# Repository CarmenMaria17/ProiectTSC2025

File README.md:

# TSC2025 Project

## Block Diagram

## Brief Description

### Microcontroller
- **ESP32-C6**: Main processor with WiFi/BLE, controls all components

### Display and Storage
- **E-Ink Display**: Minimal power consumption display
- **SD Card**: Electronic book storage
- **64MB Flash Memory**: For firmware and cache

### Power
- **USB-C**: Charging and data transfer
- **Battery charging circuit**: MCP73831 for LiPo battery
- **LiPo Battery**: 3.7V portable power
- **3.3V Regulator**: Voltage stabilizer for ESP32 and sensors

### Sensors
- **BME680**: Temperature and humidity, I2C connection

### Other Components
- **RTC DS3231**: Real-time clock for timekeeping
- **Buttons**: Navigation and control via GPIO

### Interfaces
- **SPI**: Display, SD card, flash memory
- **I2C**: Sensors, RTC
- **GPIO**: Buttons and control

## ESP32-C6 - Pin Allocation

### Communication pins
- **SPI_CLK**: Clock for SPI interface (connected to Flash, SD Card, Display)
- **SPI_MOSI**: Master Out Slave In for SPI
- **SPI_MISO**: Master In Slave Out for SPI
- **SS_SD**: Chip Select for SD Card
- **SS_FLASH**: Chip Select for Flash memory
- **SS_DISP**: Chip Select for E-Ink Display
- **I2C_SCL**: Clock for I2C interface
- **I2C_SDA**: Data line for I2C
- **EPD_DC**: Data/Command for E-Ink display
- **EPD_RST**: Reset for E-Ink display
- **EPD_BUSY**: Status signal from E-Ink display

### Other specific pins
- **RTC_INT**: Interrupt from RTC module
- **VBAT**: Battery power
- **3V3**: 3.3V power
- **GND**: Ground

# Bill of Materials

| Component | Model | Datasheet |
|-----------|--------------|-----------|
| BD5229G-TR | [Model](https://www.digikey.ee/en/models/658502) | [Datasheet](https://www.rohm.com/datasheet?p=BD5229G&dist=Digi-key&media=referral&source=digi-key.com&campaign=Digi-key) |
| ESP32 WROVER 0805 Capacitor | [Model](https://ro.mouser.com/ProductDetail/KYOCERA-AVX/SD0805S020S1R0?qs=jCA%252BPfw4LHbpkAoSnwrdjw%3D%3D) | [Datasheet](https://ro.mouser.com/datasheet/2/40/schottky-3165252.pdf) |
| 112A-TAAR-R03 | [Model](https://www.snapeda.com/parts/112A-TAAR-R03/Attend/view-part/) | [Datasheet](https://www.snapeda.com/parts/112A-TAAR-R03/Attend/datasheet/) |
| 744043680 | [Model](https://ro.mouser.com/ProductDetail/Wurth-Elektronik/744043680?qs=PGXP4M47uW6VkZq%252BkzjrHA%3D%3D) | [Datasheet](https://www.we-online.com/components/products/datasheet/744043680.pdf) |
| LED Chip 0603 | [Model](https://grabcad.com/library/0603-smd-led-1) | [Datasheet](https://www.snapeda.com/parts/KP-1608SURCK/Kingbright/datasheet/) |
| MAX17048G+T10 | [Model](https://www.snapeda.com/parts/MAX17048G+T10/Analog+Devices/view-part/?ref=eda) | [Datasheet](https://www.snapeda.com/parts/MAX17048G+T10/Analog%20Devices/datasheet/) |
| MBR0530 Schottky Diode | [Model](https://www.snapeda.com/parts/MBR0530/Onsemi/view-part/?ref=eda) | [Datasheet](https://www.snapeda.com/parts/MBR0530/ON%20Semiconductor/datasheet/) |
| PGB1010603MR | [Model](https://www.snapeda.com/parts/PGB1010603MR/Littelfuse/view-part/?ref=eda) | [Datasheet](https://www.snapeda.com/parts/PGB1010603MR/Littelfuse%20Inc./datasheet/) |
| QWIIC Connector | [Model](https://www.snapeda.com/parts/PRT-14417/SparkFun/view-part/) | [Datasheet](https://www.snapeda.com/parts/PRT-14417/SparkFun%20Electronics/datasheet/) |
| ESP32 WROVER BME680 Sensor | [Model](https://www.digikey.ro/en/models/7401317) | [Datasheet](https://www.bosch-sensortec.com/media/boschsensortec/downloads/datasheets/bst-bme680-ds001.pdf) |
| FH34SRJ-24S-0.5SH | [Model](https://www.snapeda.com/parts/FH34SRJ-24S-0.5SH(99)/Hirose/view-part/) | [Datasheet](https://www.snapeda.com/parts/FH34SRJ-24S-0.5SH(99)/Hirose%20Connector/datasheet/) |
| Resistor 0402 | [Model](https://componentsearchengine.com/part-view/R0402%201%25%20100%20K%20(RC0402FR-07100KL)/YAGEO) | [Datasheet](https://www.yageo.com/upload/media/product/products/datasheet/rchip/PYu-RC_Group_51_RoHS_L_12.pdf) |
| ESP32 WROVER MCP73831 Power Management | [Model](https://www.snapeda.com/parts/MCP73831T-2ACI/OT/Microchip/view-part/) | [Datasheet](https://www.snapeda.com/parts/MCP73831T-2ACI/OT/Microchip/datasheet/) |
| ESP32C6 Varistor 1812 | [Model](https://www.snapeda.com/parts/RC0603JR-070RL/Yageo/view-part/) | [Datasheet](https://www.snapeda.com/parts/RC0603JR-070RL/Yageo/datasheet/) |
| ESP32C6 WROOM-1-N8 | [Model](https://www.snapeda.com/parts/ESP32-C6-WROOM-1-N8/Espressif+Systems/view-part/?ref=eda) | [Datasheet](https://www.snapeda.com/parts/ESP32-C6-WROOM-1-N8/Espressif%20Systems/datasheet/) |
| Capacitor 0402 | [Model](https://componentsearchengine.com/part-view/CC0402MRX5R5BB106/YAGEO) | [Datasheet](https://componentsearchengine.com/Datasheets/2/CC0402MRX5R5BB106.pdf) |
| SI1308EDL-T1-GE3 MOSFET | [Model](https://www.snapeda.com/parts/SI1308EDL-T1-GE3/Vishay+Siliconix/view-part/?ref=eda) | [Datasheet](https://www.snapeda.com/parts/SI1308EDL-T1-GE3/Vishay%20Siliconix/datasheet/) |
| SJ | [Model](https://grabcad.com/library/solder-jumpers-1) | [Datasheet]() |
| CPH3225A | [Model](https://www.snapeda.com/parts/CPH3225A/Seiko+Instruments/view-part/?ref=eda) | [Datasheet](https://www.snapeda.com/parts/CPH3225A/Seiko%20Instruments/datasheet/) |
| Button | [Model](https://industry.panasonic.com/global/en/products/control/switch/light-touch/number/evqpuj02k) | [Datasheet](https://industry.panasonic.com/global/en/downloads?tab=catalog&small_g_cd=203&part_no=EVQPUJ02K) |
| DS3231SN | [Model](https://www.snapeda.com/parts/DS3231SN%23/Analog+Devices/view-part/?ref=eda) | [Datasheet](https://www.snapeda.com/parts/DS3231SN%23/Analog%20Devices/datasheet/) |
| USBLC6-2SC6Y | [Model](https://www.snapeda.com/parts/USBLC6-2SC6Y/STMicroelectronics/view-part/?ref=eda) | [Datasheet](https://www.snapeda.com/parts/USBLC6-2SC6Y/STMicroelectronics/datasheet/) |
| W25Q512JVEIQ | [Model](https://www.digikey.ro/en/models/10244706) | [Datasheet](https://www.winbond.com/resource-files/W25Q512JV%20SPI%20RevB%2006252019%20KMS.pdf) |
| XC6220A331MR-G | [Model](https://componentsearchengine.com/part-view/XC6220A331MR-G/Torex) | [Datasheet](https://product.torexsemi.com/system/files/series/xc6220.pdf) |
| TPTP20R | [Model](https://ro.mouser.com/ProductDetail/Adafruit/3825?qs=%252bEew9%252b0nqrAn6n76%252bB5vZg%3D%3D&utm_source=findchips&utm_medium=aggregator&utm_campaign=3825&utm_term=3825&utm_content=Adafruit&_gl=1*1t6jdbp*_ga*MTQ5NTQ1ODI1LjE3NDMyMzgzNTY.*_ga_15W4STQT4T*MTc0Mzc4MDU5Ni4xMi4xLjE3NDM3ODM2MzIuNDIuMC4w) | [Datasheet](https://cdn-shop.adafruit.com/product-files/3825/3825_diagram.PDF) |
| USB4110-GF-A | [Model](https://componentsearchengine.com/part-view/USB4110-GF-A/GCT%20(GLOBAL%20CONNECTOR%20TECHNOLOGY)) | [Datasheet](https://gct.co/files/drawings/usb4110.pdf) |

# Power Consumption Estimation

The ESP32-C6 microcontroller with Wi-Fi active draws approximately 200mA at 3.3V, consuming around 660mW of power.

For display operations, the 1.5" E-Ink display requires about 40mA (132mW) during refresh cycles.

The BME680 environmental sensor consumes minimal power at just 3.1mA (10.23mW) during measurement operations and can be put into sleep mode between readings.

The DS3231 RTC module is extremely efficient, drawing only 0.15mA (0.495mW) while maintaining accurate timekeeping.

Storage components include the SD card for e-book storage that requires 50mA (165mW) during active read/write operations, and the 64MB external flash memory that draws about 25mA (82.5mW) when accessed.

In total, the maximum estimated power consumption is approximately 318.25mA at 3.3V, resulting in 1050.72mW during peak usage.

# Other images

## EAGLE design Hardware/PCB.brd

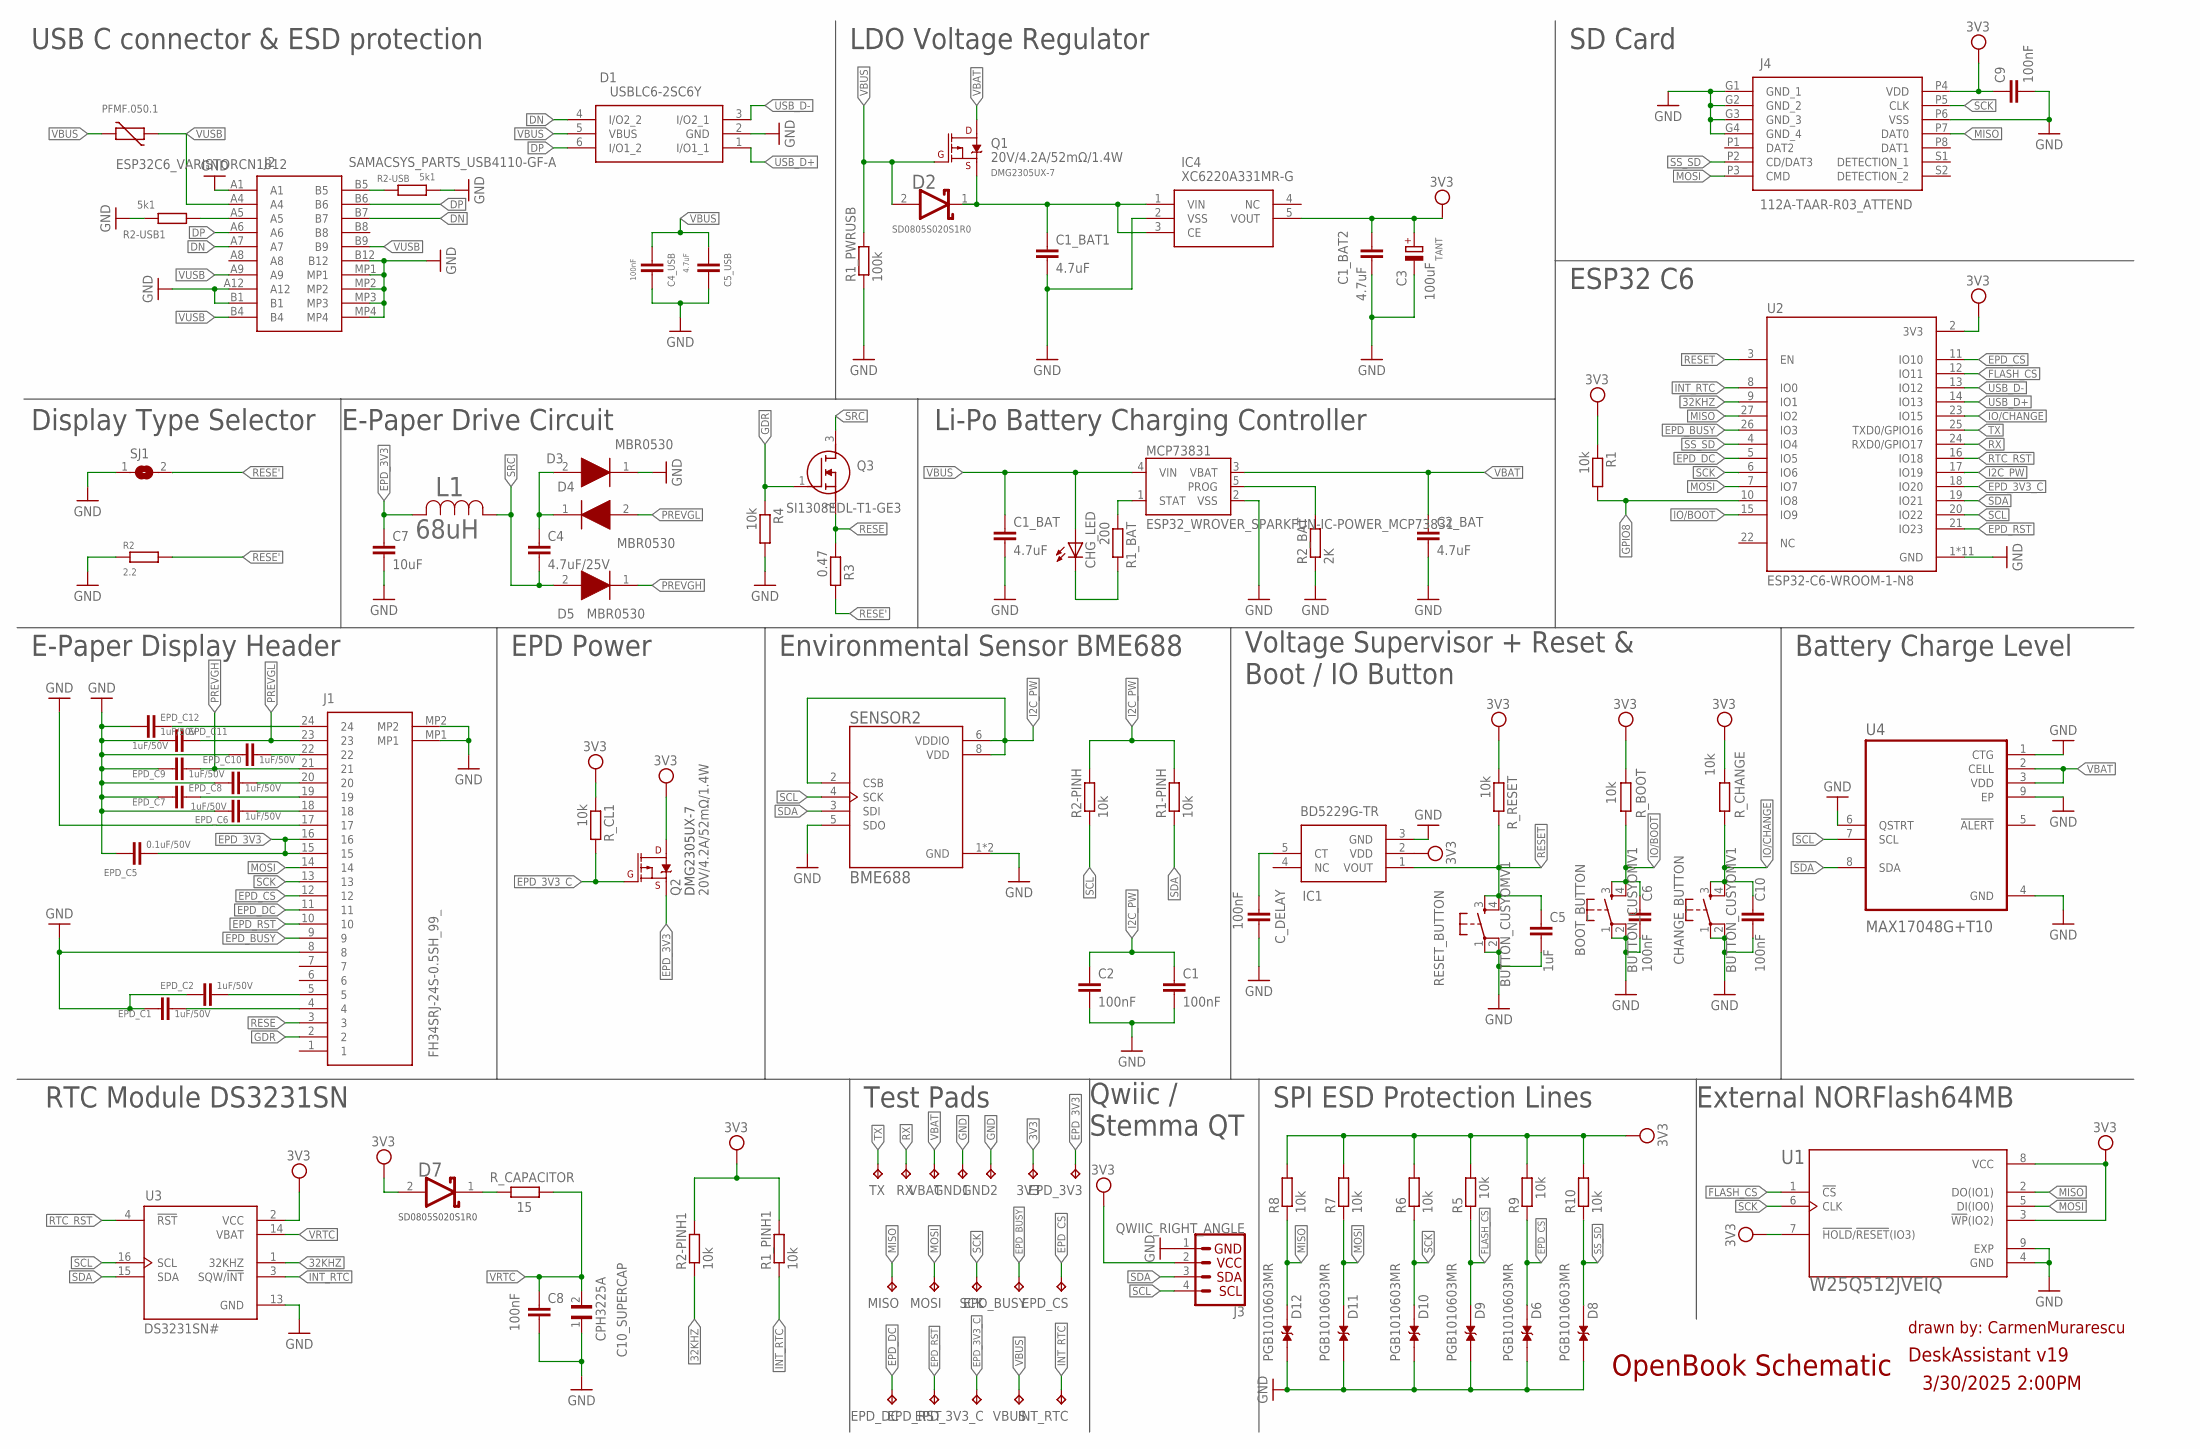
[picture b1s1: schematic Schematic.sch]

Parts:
3V3: TPTP20R; TP20R
BOOT_BUTTON: BUTTON_CUSYOMV1; MYBUTTON
C1, C2, C4_USB, C6, C8, C9, C10: 100nF; ESP32_WROVER_EAGLE-LTSPICE_C0402
C1_BAT, C1_BAT1, C1_BAT2, C2_BAT, C5_USB: 4.7uF; ESP32_WROVER_EAGLE-LTSPICE_C0402
C3: 100uF; RCL_CT3528
C4: 4.7uF/25V; ESP32_WROVER_EAGLE-LTSPICE_C0402
C5: 1uF; ESP32_WROVER_EAGLE-LTSPICE_C0402
C7: 10uF; ESP32_WROVER_EAGLE-LTSPICE_C0402
C10_SUPERCAP: CPH3225A; CAPCP3225X100N
CHANGE_BUTTON: BUTTON_CUSYOMV1; MYBUTTON
CHG_LED: ADAFRUIT_LEDCHIP-LED0603; ADAFRUIT_CHIP-LED0603
C_DELAY: 100nF; ESP32_WROVER_EAGLE-LTSPICE_C0402
D1: USBLC6-2SC6Y; SOT95P280X145-6N
D2: ESP32_WROVER_AVX---SD0805S020S1R0_AVX_SD0805S020S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; ESP32_WROVER_AVX---SD0805S020S1R0_AVX_SD0805S020S1R0_0
D3, D4, D5: MBR0530; SOD3716X135N
D6, D8, D9, D10, D11, D12: PGB1010603MR; DIOC1608X36N
D7: SD0805S020S1R0; ESP32_WROVER_AVX---SD0805S020S1R0_AVX_SD0805S020S1R0_0
EPD_3V3, EPD_3V3_C: TPTP20R; TP20R
EPD_BUSY: TPTP20R; TP20R
EPD_C1, EPD_C2, EPD_C6, EPD_C7, EPD_C8, EPD_C9, EPD_C10, EPD_C11, EPD_C12: 1uF/50V; ESP32_WROVER_EAGLE-LTSPICE_C0402
EPD_C5: 0.1uF/50V; ESP32_WROVER_EAGLE-LTSPICE_C0402
EPD_CS: TPTP20R; TP20R
EPD_DC: TPTP20R; TP20R
EPD_RST: TPTP20R; TP20R
GND1, GND2: TPTP20R; TP20R
IC1: BD5229G-TR; SOT95P280X120-5N
IC4: XC6220A331MR-G; SOT95P280X120-5N
INT_RTC: TPTP20R; TP20R
J1: FH34SRJ-24S-0.5SH_99_; FH34SRJ24S05SH99
J2: SAMACSYS_PARTS_USB4110-GF-A; SAMACSYS_PARTS_USB4110GFA
J3: QWIIC_RIGHT_ANGLE; JST04_1MM_RA
J4: 112A-TAAR-R03_ATTEND; 112ATAARR03ATTEND
L1: 68uH; IND_4828-WE-TPC_WRE
MCP73831: ESP32_WROVER_SPARKFUN-IC-POWER_MCP73831; ESP32_WROVER_SPARKFUN-IC-POWER_SOT23-5
MISO: TPTP20R; TP20R
MOSI: TPTP20R; TP20R
PFMF.050.1: ESP32C6_VARISTORCN1812; ESP32C6_VARISTOR_CT/CN1812
Q1, Q2: 20V/4.2A/52mΩ/1.4W; ESP32_WROVER_SPARKFUN-DISCRETESEMI_SOT23-3
Q3: SI1308EDL-T1-GE3; SOT65P210X110-3N
R1, R1-PINH, R1_PINH1, R2-PINH, R2-PINH1, R4, R5, R6, R7, R8, R9, R10: 10k; ESP32_WROVER_EAGLE-LTSPICE_R0402
R1_BAT: 200; ESP32_WROVER_EAGLE-LTSPICE_R0402
R1_PWRUSB: 100k; ESP32_WROVER_EAGLE-LTSPICE_R0402
R2: 2.2; ESP32_WROVER_EAGLE-LTSPICE_R0402
R2-USB, R2-USB1: 5k1; ESP32_WROVER_EAGLE-LTSPICE_R0402
R2_BAT: 2K; ESP32_WROVER_EAGLE-LTSPICE_R0402
R3: 0.47; ESP32_WROVER_EAGLE-LTSPICE_R0402
RESET_BUTTON: BUTTON_CUSYOMV1; MYBUTTON
RX: TPTP20R; TP20R
R_BOOT: 10k; ESP32_WROVER_EAGLE-LTSPICE_R0402
R_CAPACITOR: 15; ESP32_WROVER_EAGLE-LTSPICE_R0402
R_CHANGE: 10k; ESP32_WROVER_EAGLE-LTSPICE_R0402
R_CL1: 10k; ESP32_WROVER_EAGLE-LTSPICE_R0402
R_RESET: 10k; ESP32_WROVER_EAGLE-LTSPICE_R0402
SCK: TPTP20R; TP20R
SENSOR2: BME688; ESP32_WROVER_BME680_PSON80P300X300X100-8N
SJ1: SJ
TX: TPTP20R; TP20R
U1: W25Q512JVEIQ; SON127P600X800X80-9N
U2: ESP32-C6-WROOM-1-N8; XCVR_ESP32-C6-WROOM-1-N8
U3: DS3231SN#; SOIC127P1032X265-16N
U4: MAX17048G+T10; SON50P200X200X80-9N
VBAT: TPTP20R; TP20R
VBUS: TPTP20R; TP20R

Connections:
3V3: 3V3.TP, C1_BAT2.1, C3.+, C9.1, D7.2 (ANODE), IC1.2 (VDD), IC4.5 (VOUT), J3.2, J4.P4 (VDD), Q2.3 (D), R1.1, R1_PINH1.2, R2-PINH1.2, R5.2, R6.2, R7.2, R8.2, R9.2, R10.2, R_BOOT.2, R_CHANGE.2, R_CL1.1, R_RESET.1, U1.3 (!WP!(IO2)), U1.7 (!HOLD!/!RESET!(IO3)), U1.8 (VCC), U2.2 (3V3), U3.2 (VCC)
32KHZ: R2-PINH1.1, U2.9 (IO1), U3.1 (32KHZ)
DN: D1.4 (I/O2_2), J2.A7, J2.B7
DP: D1.6 (I/O1_2), J2.A6, J2.B6
EPD_3V3: C7.1, EPD_3V3.TP, EPD_C5.1, J1.15, J1.16, L1.2, Q2.2 (S)
EPD_3V3_C: EPD_3V3_C.TP, Q2.1 (G), R_CL1.2, U2.18 (IO20)
EPD_BUSY: EPD_BUSY.TP, J1.9, U2.26 (IO3)
EPD_CS: D6.2, EPD_CS.TP, J1.12, R9.1, U2.11 (IO10)
EPD_DC: EPD_DC.TP, J1.11, U2.5 (IO5)
EPD_RST: EPD_RST.TP, J1.10, U2.21 (IO23)
FLASH_CS: D9.2, R5.1, U1.1 (!CS), U2.12 (IO11)
GDR: J1.2, Q3.1 (G), R4.1
GND: BOOT_BUTTON.1, BOOT_BUTTON.2, C1.2, C1_BAT.2, C1_BAT1.2, C1_BAT2.2, C2.2, C2_BAT.2, C3.-, C4_USB.2, C5.2, C5_USB.2, C6.2, C7.2, C8.2, C9.2, C10.2, C10_SUPERCAP.1, CHANGE_BUTTON.1, CHANGE_BUTTON.2, C_DELAY.2, D1.2 (GND), D4.1 (K), D6.1, D8.1, D9.1, D10.1, D11.1, D12.1, EPD_C1.2, EPD_C2.2, EPD_C5.2, EPD_C6.2, EPD_C7.2, EPD_C8.2, EPD_C9.2, EPD_C10.2, EPD_C11.2, EPD_C12.2, GND1.TP, GND2.TP, IC1.3 (GND), IC4.2 (VSS), J1.8, J1.17, J1.MP1, J1.MP2, J2.A1, J2.A12, J2.B1, J2.B12, J2.MP1, J2.MP2, J2.MP3, J2.MP4, J3.1, J4.G1 (GND_1), J4.G2 (GND_2), J4.G3 (GND_3), J4.G4 (GND_4), J4.P6 (VSS), MCP73831.2 (VSS), R1_PWRUSB.1, R2.1, R2-USB.2, R2-USB1.1, R2_BAT.1, R4.2, RESET_BUTTON.1, RESET_BUTTON.2, SENSOR2.1 (GND), SENSOR2.5 (SDO), SENSOR2.7 (GND), SJ1.1, U1.4 (GND), U1.9 (EXP), U2.1 (GND), U2.28 (GND), U2.29_1 (GND), U2.29_2 (GND), U2.29_3 (GND), U2.29_4 (GND), U2.29_5 (GND), U2.29_6 (GND), U2.29_7 (GND), U2.29_8 (GND), U2.29_9 (GND), U3.13 (GND), U4.1 (CTG), U4.4 (GND), U4.6 (QSTRT), U4.9 (EP)
GPIO8: R1.2, U2.10 (IO8)
I2C_PW: C1.1, C2.1, R1-PINH.2, R2-PINH.2, SENSOR2.2 (CSB), SENSOR2.6 (VDDIO), SENSOR2.8 (VDD), U2.17 (IO19)
INT_RTC: INT_RTC.TP, R1_PINH1.1, U2.8 (IO0), U3.3 (SQW/!INT)
IO/BOOT: BOOT_BUTTON.3, BOOT_BUTTON.4, C6.1, R_BOOT.1, U2.15 (IO9)
IO/CHANGE: C10.1, CHANGE_BUTTON.3, CHANGE_BUTTON.4, R_CHANGE.1, U2.23 (IO15)
MISO: D12.2, J4.P7 (DAT0), MISO.TP, R8.1, U1.2 (DO(IO1)), U2.27 (IO2)
MOSI: D11.2, J1.14, J4.P3 (CMD), MOSI.TP, R7.1, U1.5 (DI(IO0)), U2.7 (IO7)
unnamed: J2.A5, R2-USB1.2
unnamed: J2.B5, R2-USB.1
unnamed: C1_BAT1.1, D2.1 (CATHODE), IC4.1 (VIN), IC4.3 (CE), Q1.2 (S)
unnamed: C4.1, D3.1 (K), D4.2 (A)
unnamed: CHG_LED.C, R1_BAT.2
unnamed: MCP73831.1 (STAT), R1_BAT.1
unnamed: EPD_C6.1, J1.18
unnamed: MCP73831.5 (PROG), R2_BAT.2
unnamed: EPD_C1.1, J1.4
unnamed: EPD_C2.1, J1.5
unnamed: EPD_C7.1, J1.19
unnamed: EPD_C8.1, J1.20
unnamed: D7.1 (CATHODE), R_CAPACITOR.2
unnamed: EPD_C10.1, J1.22
unnamed: C_DELAY.1, IC1.5 (CT)
unnamed: EPD_C12.1, J1.24
PREVGH: D5.1 (K), EPD_C9.1, J1.21
PREVGL: D3.2 (A), EPD_C11.1, J1.23
RESE: J1.3, Q3.2 (S), R3.1
RESE': R2.2, R3.2, SJ1.2
RESET: C5.1, IC1.1 (VOUT), RESET_BUTTON.3, RESET_BUTTON.4, R_RESET.2, U2.3 (EN)
RTC_RST: U2.16 (IO18), U3.4 (!RST)
RX: RX.TP, U2.24 (RXD0/GPIO17)
SCK: D10.2, J1.13, J4.P5 (CLK), R6.1, SCK.TP, U1.6 (CLK), U2.6 (IO6)
SCL: J3.4, R2-PINH.1, SENSOR2.4 (SCK), U2.20 (IO22), U3.16 (SCL), U4.7 (SCL)
SDA: J3.3, R1-PINH.1, SENSOR2.3 (SDI), U2.19 (IO21), U3.15 (SDA), U4.8 (SDA)
SRC: C4.2, D5.2 (A), L1.1, Q3.3 (D)
SS_SD: D8.2, J4.P2 (CD/DAT3), R10.1, U2.4 (IO4)
TX: TX.TP, U2.25 (TXD0/GPIO16)
USB_D+: D1.1 (I/O1_1), U2.14 (IO13)
USB_D-: D1.3 (I/O2_1), U2.13 (IO12)
VBAT: C2_BAT.1, MCP73831.3 (VBAT), Q1.3 (D), U4.2 (CELL), U4.3 (VDD), VBAT.TP
VBUS: C1_BAT.1, C4_USB.1, C5_USB.1, CHG_LED.A, D1.5 (VBUS), D2.2 (ANODE), MCP73831.4 (VIN), PFMF.050.1.2, Q1.1 (G), R1_PWRUSB.2, VBUS.TP
VRTC: C8.1, C10_SUPERCAP.2, R_CAPACITOR.1, U3.14 (VBAT)
VUSB: J2.A4, J2.A9, J2.B4, J2.B9, PFMF.050.1.1

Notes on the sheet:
USB C connector & ESD protection
LDO Voltage Regulator
SD Card
Display Type Selector
E-Paper Drive Circuit
Li-Po Battery Charging Controller
ESP32 C6
E-Paper Display Header
EPD Power
Environmental Sensor BME688
Voltage Supervisor + Reset & Boot / IO Button
Battery Charge Level
RTC Module DS3231SN
Test Pads
Qwiic / Stemma QT
SPI ESD Protection Lines
External NORFlash64MB
OpenBook Schematic
drawn by: CarmenMurarescu
DeskAssistant v19
3/30/2025 2:00PM
DMG2305UX-7
SD0805S020S1R0
TANT

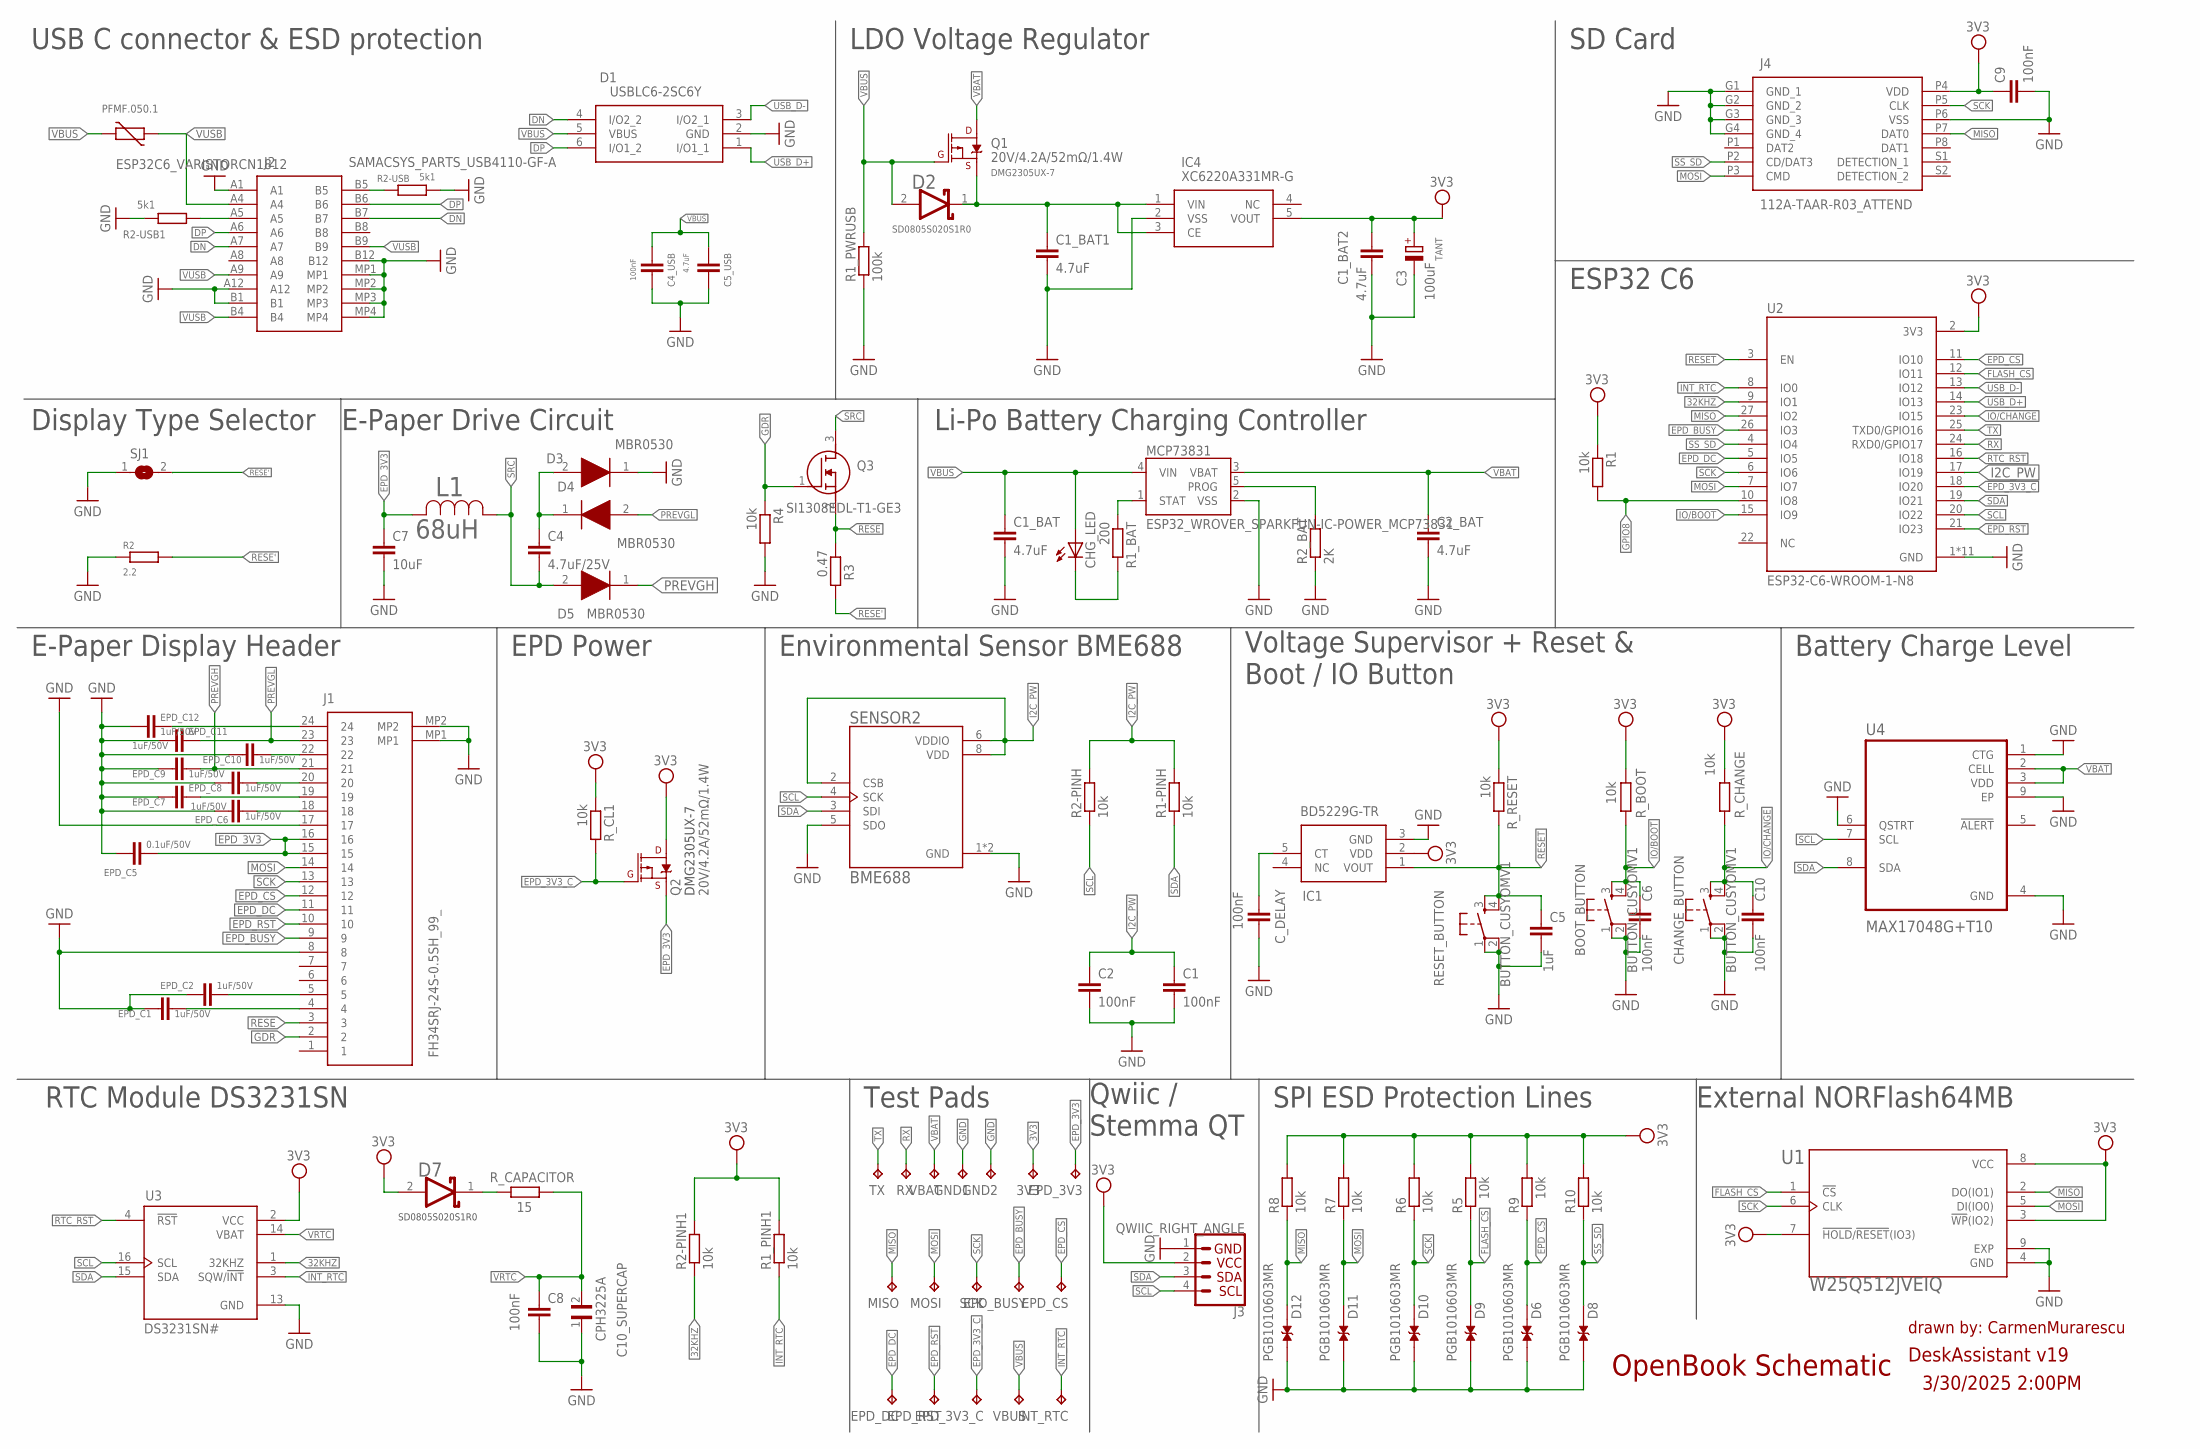
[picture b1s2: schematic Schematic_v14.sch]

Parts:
3V3: TPTP20R; TP20R
BOOT_BUTTON: BUTTON_CUSYOMV1; MYBUTTON
C1, C2, C4_USB, C6, C8, C9, C10: 100nF; ESP32_WROVER_EAGLE-LTSPICE_C0402
C1_BAT, C1_BAT1, C1_BAT2, C2_BAT, C5_USB: 4.7uF; ESP32_WROVER_EAGLE-LTSPICE_C0402
C3: 100uF; RCL_CT3528
C4: 4.7uF/25V; ESP32_WROVER_EAGLE-LTSPICE_C0402
C5: 1uF; ESP32_WROVER_EAGLE-LTSPICE_C0402
C7: 10uF; ESP32_WROVER_EAGLE-LTSPICE_C0402
C10_SUPERCAP: CPH3225A; CAPCP3225X100N
CHANGE_BUTTON: BUTTON_CUSYOMV1; MYBUTTON
CHG_LED: ADAFRUIT_LEDCHIP-LED0603; ADAFRUIT_CHIP-LED0603
C_DELAY: 100nF; ESP32_WROVER_EAGLE-LTSPICE_C0402
D1: USBLC6-2SC6Y; SOT95P280X145-6N
D2: ESP32_WROVER_AVX---SD0805S020S1R0_AVX_SD0805S020S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; ESP32_WROVER_AVX---SD0805S020S1R0_AVX_SD0805S020S1R0_0
D3, D4, D5: MBR0530; SOD3716X135N
D6, D8, D9, D10, D11, D12: PGB1010603MR; DIOC1608X36N
D7: SD0805S020S1R0; ESP32_WROVER_AVX---SD0805S020S1R0_AVX_SD0805S020S1R0_0
EPD_3V3, EPD_3V3_C: TPTP20R; TP20R
EPD_BUSY: TPTP20R; TP20R
EPD_C1, EPD_C2, EPD_C6, EPD_C7, EPD_C8, EPD_C9, EPD_C10, EPD_C11, EPD_C12: 1uF/50V; ESP32_WROVER_EAGLE-LTSPICE_C0402
EPD_C5: 0.1uF/50V; ESP32_WROVER_EAGLE-LTSPICE_C0402
EPD_CS: TPTP20R; TP20R
EPD_DC: TPTP20R; TP20R
EPD_RST: TPTP20R; TP20R
GND1, GND2: TPTP20R; TP20R
IC1: BD5229G-TR; SOT95P280X120-5N
IC4: XC6220A331MR-G; SOT95P280X120-5N
INT_RTC: TPTP20R; TP20R
J1: FH34SRJ-24S-0.5SH_99_; FH34SRJ24S05SH99
J2: SAMACSYS_PARTS_USB4110-GF-A; SAMACSYS_PARTS_USB4110GFA
J3: QWIIC_RIGHT_ANGLE; JST04_1MM_RA
J4: 112A-TAAR-R03_ATTEND; 112ATAARR03ATTEND
L1: 68uH; IND_4828-WE-TPC_WRE
MCP73831: ESP32_WROVER_SPARKFUN-IC-POWER_MCP73831; ESP32_WROVER_SPARKFUN-IC-POWER_SOT23-5
MISO: TPTP20R; TP20R
MOSI: TPTP20R; TP20R
PFMF.050.1: ESP32C6_VARISTORCN1812; ESP32C6_VARISTOR_CT/CN1812
Q1, Q2: 20V/4.2A/52mΩ/1.4W; ESP32_WROVER_SPARKFUN-DISCRETESEMI_SOT23-3
Q3: SI1308EDL-T1-GE3; SOT65P210X110-3N
R1, R1-PINH, R1_PINH1, R2-PINH, R2-PINH1, R4, R5, R6, R7, R8, R9, R10: 10k; ESP32_WROVER_EAGLE-LTSPICE_R0402
R1_BAT: 200; ESP32_WROVER_EAGLE-LTSPICE_R0402
R1_PWRUSB: 100k; ESP32_WROVER_EAGLE-LTSPICE_R0402
R2: 2.2; ESP32_WROVER_EAGLE-LTSPICE_R0402
R2-USB, R2-USB1: 5k1; ESP32_WROVER_EAGLE-LTSPICE_R0402
R2_BAT: 2K; ESP32_WROVER_EAGLE-LTSPICE_R0402
R3: 0.47; ESP32_WROVER_EAGLE-LTSPICE_R0402
RESET_BUTTON: BUTTON_CUSYOMV1; MYBUTTON
RX: TPTP20R; TP20R
R_BOOT: 10k; ESP32_WROVER_EAGLE-LTSPICE_R0402
R_CAPACITOR: 15; ESP32_WROVER_EAGLE-LTSPICE_R0402
R_CHANGE: 10k; ESP32_WROVER_EAGLE-LTSPICE_R0402
R_CL1: 10k; ESP32_WROVER_EAGLE-LTSPICE_R0402
R_RESET: 10k; ESP32_WROVER_EAGLE-LTSPICE_R0402
SCK: TPTP20R; TP20R
SENSOR2: BME688; ESP32_WROVER_BME680_PSON80P300X300X100-8N
SJ1: SJ
TX: TPTP20R; TP20R
U1: W25Q512JVEIQ; SON127P600X800X80-9N
U2: ESP32-C6-WROOM-1-N8; XCVR_ESP32-C6-WROOM-1-N8
U3: DS3231SN#; SOIC127P1032X265-16N
U4: MAX17048G+T10; SON50P200X200X80-9N
VBAT: TPTP20R; TP20R
VBUS: TPTP20R; TP20R

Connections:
3V3: 3V3.TP, C1_BAT2.1, C3.+, C9.1, D7.2 (ANODE), IC1.2 (VDD), IC4.5 (VOUT), J3.2, J4.P4 (VDD), Q2.3 (D), R1.1, R1_PINH1.2, R2-PINH1.2, R5.2, R6.2, R7.2, R8.2, R9.2, R10.2, R_BOOT.2, R_CHANGE.2, R_CL1.1, R_RESET.1, U1.3 (!WP!(IO2)), U1.7 (!HOLD!/!RESET!(IO3)), U1.8 (VCC), U2.2 (3V3), U3.2 (VCC)
32KHZ: R2-PINH1.1, U2.9 (IO1), U3.1 (32KHZ)
DN: D1.4 (I/O2_2), J2.A7, J2.B7
DP: D1.6 (I/O1_2), J2.A6, J2.B6
EPD_3V3: C7.1, EPD_3V3.TP, EPD_C5.1, J1.15, J1.16, L1.2, Q2.2 (S)
EPD_3V3_C: EPD_3V3_C.TP, Q2.1 (G), R_CL1.2, U2.18 (IO20)
EPD_BUSY: EPD_BUSY.TP, J1.9, U2.26 (IO3)
EPD_CS: D6.2, EPD_CS.TP, J1.12, R9.1, U2.11 (IO10)
EPD_DC: EPD_DC.TP, J1.11, U2.5 (IO5)
EPD_RST: EPD_RST.TP, J1.10, U2.21 (IO23)
FLASH_CS: D9.2, R5.1, U1.1 (!CS), U2.12 (IO11)
GDR: J1.2, Q3.1 (G), R4.1
GND: BOOT_BUTTON.1, BOOT_BUTTON.2, C1.2, C1_BAT.2, C1_BAT1.2, C1_BAT2.2, C2.2, C2_BAT.2, C3.-, C4_USB.2, C5.2, C5_USB.2, C6.2, C7.2, C8.2, C9.2, C10.2, C10_SUPERCAP.1, CHANGE_BUTTON.1, CHANGE_BUTTON.2, C_DELAY.2, D1.2 (GND), D4.1 (K), D6.1, D8.1, D9.1, D10.1, D11.1, D12.1, EPD_C1.2, EPD_C2.2, EPD_C5.2, EPD_C6.2, EPD_C7.2, EPD_C8.2, EPD_C9.2, EPD_C10.2, EPD_C11.2, EPD_C12.2, GND1.TP, GND2.TP, IC1.3 (GND), IC4.2 (VSS), J1.8, J1.17, J1.MP1, J1.MP2, J2.A1, J2.A12, J2.B1, J2.B12, J2.MP1, J2.MP2, J2.MP3, J2.MP4, J3.1, J4.G1 (GND_1), J4.G2 (GND_2), J4.G3 (GND_3), J4.G4 (GND_4), J4.P6 (VSS), MCP73831.2 (VSS), R1_PWRUSB.1, R2.1, R2-USB.2, R2-USB1.1, R2_BAT.1, R4.2, RESET_BUTTON.1, RESET_BUTTON.2, SENSOR2.1 (GND), SENSOR2.5 (SDO), SENSOR2.7 (GND), SJ1.1, U1.4 (GND), U1.9 (EXP), U2.1 (GND), U2.28 (GND), U2.29_1 (GND), U2.29_2 (GND), U2.29_3 (GND), U2.29_4 (GND), U2.29_5 (GND), U2.29_6 (GND), U2.29_7 (GND), U2.29_8 (GND), U2.29_9 (GND), U3.13 (GND), U4.1 (CTG), U4.4 (GND), U4.6 (QSTRT), U4.9 (EP)
GPIO8: R1.2, U2.10 (IO8)
I2C_PW: C1.1, C2.1, R1-PINH.2, R2-PINH.2, SENSOR2.2 (CSB), SENSOR2.6 (VDDIO), SENSOR2.8 (VDD), U2.17 (IO19)
INT_RTC: INT_RTC.TP, R1_PINH1.1, U2.8 (IO0), U3.3 (SQW/!INT)
IO/BOOT: BOOT_BUTTON.3, BOOT_BUTTON.4, C6.1, R_BOOT.1, U2.15 (IO9)
IO/CHANGE: C10.1, CHANGE_BUTTON.3, CHANGE_BUTTON.4, R_CHANGE.1, U2.23 (IO15)
MISO: D12.2, J4.P7 (DAT0), MISO.TP, R8.1, U1.2 (DO(IO1)), U2.27 (IO2)
MOSI: D11.2, J1.14, J4.P3 (CMD), MOSI.TP, R7.1, U1.5 (DI(IO0)), U2.7 (IO7)
unnamed: J2.A5, R2-USB1.2
unnamed: J2.B5, R2-USB.1
unnamed: C1_BAT1.1, D2.1 (CATHODE), IC4.1 (VIN), IC4.3 (CE), Q1.2 (S)
unnamed: C4.1, D3.1 (K), D4.2 (A)
unnamed: CHG_LED.C, R1_BAT.2
unnamed: MCP73831.1 (STAT), R1_BAT.1
unnamed: EPD_C6.1, J1.18
unnamed: MCP73831.5 (PROG), R2_BAT.2
unnamed: EPD_C1.1, J1.4
unnamed: EPD_C2.1, J1.5
unnamed: EPD_C7.1, J1.19
unnamed: EPD_C8.1, J1.20
unnamed: D7.1 (CATHODE), R_CAPACITOR.2
unnamed: EPD_C10.1, J1.22
unnamed: C_DELAY.1, IC1.5 (CT)
unnamed: EPD_C12.1, J1.24
PREVGH: D5.1 (K), EPD_C9.1, J1.21
PREVGL: D3.2 (A), EPD_C11.1, J1.23
RESE: J1.3, Q3.2 (S), R3.1
RESE': R2.2, R3.2, SJ1.2
RESET: C5.1, IC1.1 (VOUT), RESET_BUTTON.3, RESET_BUTTON.4, R_RESET.2, U2.3 (EN)
RTC_RST: U2.16 (IO18), U3.4 (!RST)
RX: RX.TP, U2.24 (RXD0/GPIO17)
SCK: D10.2, J1.13, J4.P5 (CLK), R6.1, SCK.TP, U1.6 (CLK), U2.6 (IO6)
SCL: J3.4, R2-PINH.1, SENSOR2.4 (SCK), U2.20 (IO22), U3.16 (SCL), U4.7 (SCL)
SDA: J3.3, R1-PINH.1, SENSOR2.3 (SDI), U2.19 (IO21), U3.15 (SDA), U4.8 (SDA)
SRC: C4.2, D5.2 (A), L1.1, Q3.3 (D)
SS_SD: D8.2, J4.P2 (CD/DAT3), R10.1, U2.4 (IO4)
TX: TX.TP, U2.25 (TXD0/GPIO16)
USB_D+: D1.1 (I/O1_1), U2.14 (IO13)
USB_D-: D1.3 (I/O2_1), U2.13 (IO12)
VBAT: C2_BAT.1, MCP73831.3 (VBAT), Q1.3 (D), U4.2 (CELL), U4.3 (VDD), VBAT.TP
VBUS: C1_BAT.1, C4_USB.1, C5_USB.1, CHG_LED.A, D1.5 (VBUS), D2.2 (ANODE), MCP73831.4 (VIN), PFMF.050.1.2, Q1.1 (G), R1_PWRUSB.2, VBUS.TP
VRTC: C8.1, C10_SUPERCAP.2, R_CAPACITOR.1, U3.14 (VBAT)
VUSB: J2.A4, J2.A9, J2.B4, J2.B9, PFMF.050.1.1

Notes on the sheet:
USB C connector & ESD protection
LDO Voltage Regulator
SD Card
Display Type Selector
E-Paper Drive Circuit
Li-Po Battery Charging Controller
ESP32 C6
E-Paper Display Header
EPD Power
Environmental Sensor BME688
Voltage Supervisor + Reset & Boot / IO Button
Battery Charge Level
RTC Module DS3231SN
Test Pads
Qwiic / Stemma QT
SPI ESD Protection Lines
External NORFlash64MB
OpenBook Schematic
drawn by: CarmenMurarescu
DeskAssistant v19
3/30/2025 2:00PM
DMG2305UX-7
SD0805S020S1R0
TANT

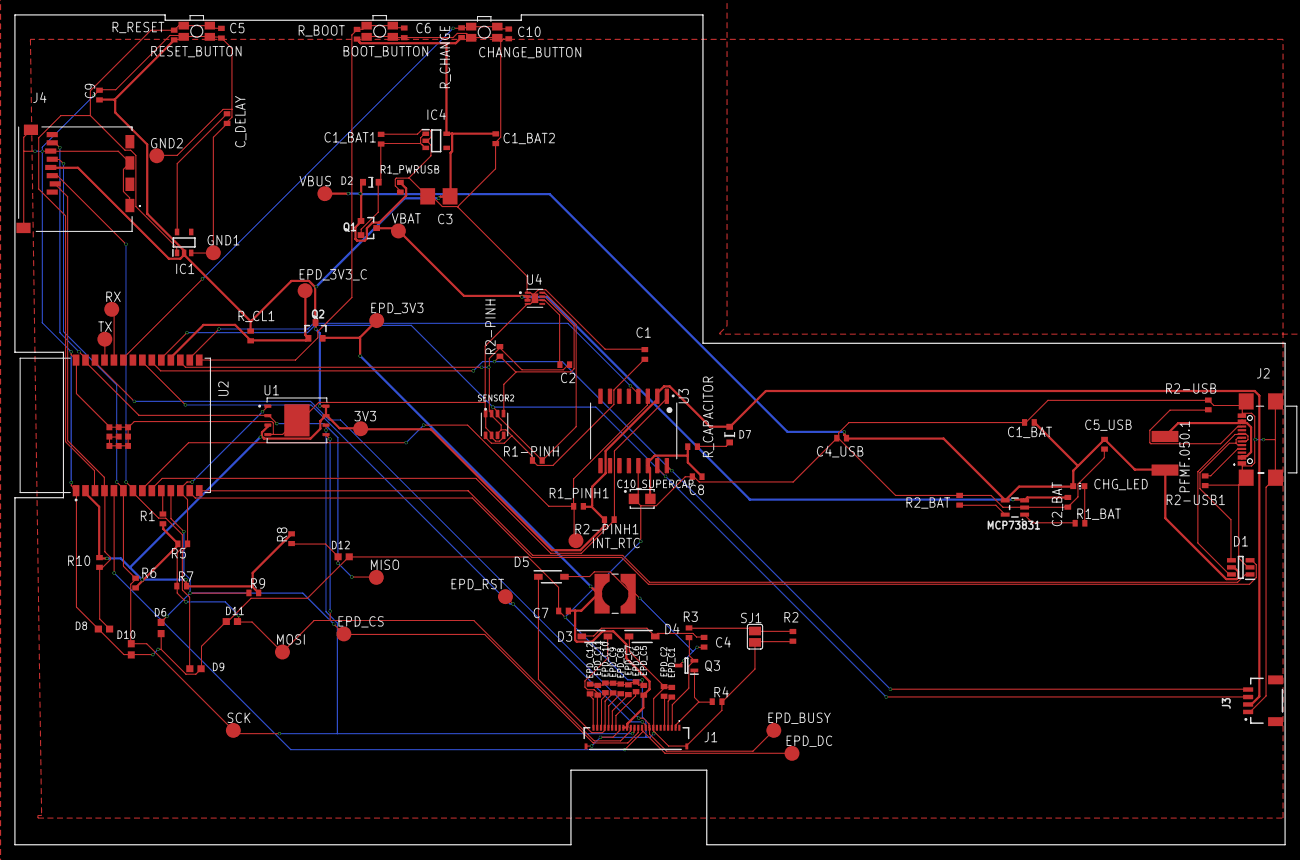
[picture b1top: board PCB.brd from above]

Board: 2 copper layers, 170.2 x 111.2 mm, 103 parts (0 on the bottom side), 55 nets.

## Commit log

2025-04-06 Create g
2025-04-06 Add files via upload
    Schematicul
2025-04-06 Create ff
2025-04-06 Create dd
2025-04-06 Create ggg
2025-04-06 Add files via upload
    pcb
2025-04-06 toate fisierele (gerber, pick and place si BOM
2025-04-06 Create LICENSE
2025-04-14 - update dupa issues
2025-04-14 Am actualizat fisierele la varianta finala

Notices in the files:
parts and their libraries:
COPYRIGHT: Copyright (C) 2024 Ultra Librarian. All rights reserved.
